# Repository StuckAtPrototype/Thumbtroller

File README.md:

# Thumbtroller - StuckAtPrototype

Remote for the racer car project

https://github.com/StuckAtPrototype/Racer

## Youtube Video
A bit of a back-story of how this project came to be.

Sub if you like what you see.

## Project Structure
The project consists of
1. Firmware
2. Hardware
3. Mechanical 

#### Requirements
- ESP-IDF 5.5
- Git (for cloning ESP-IDF and this repo; see [BUILD_WINDOWS.md](BUILD_WINDOWS.md) if you need to install it)
- Target set to ESP32-H2

**Windows:** See [BUILD_WINDOWS.md](BUILD_WINDOWS.md) for a step-by-step guide: install Git if needed, clone ESP-IDF 5.5, build, and flash the firmware using Command Prompt.

---
## License
### Apache 2.0 -- i.e. use as you'd like
http://www.apache.org/licenses/LICENSE-2.0

--- 
## Special Thanks
Thanks to Michael Angerer for his open sourced `esp32_ble_ota` project. I used it to get BLE running in this project. His blog post and github repo are a great resource. Check it out. https://github.com/michael-angerer/esp32_ble_ota

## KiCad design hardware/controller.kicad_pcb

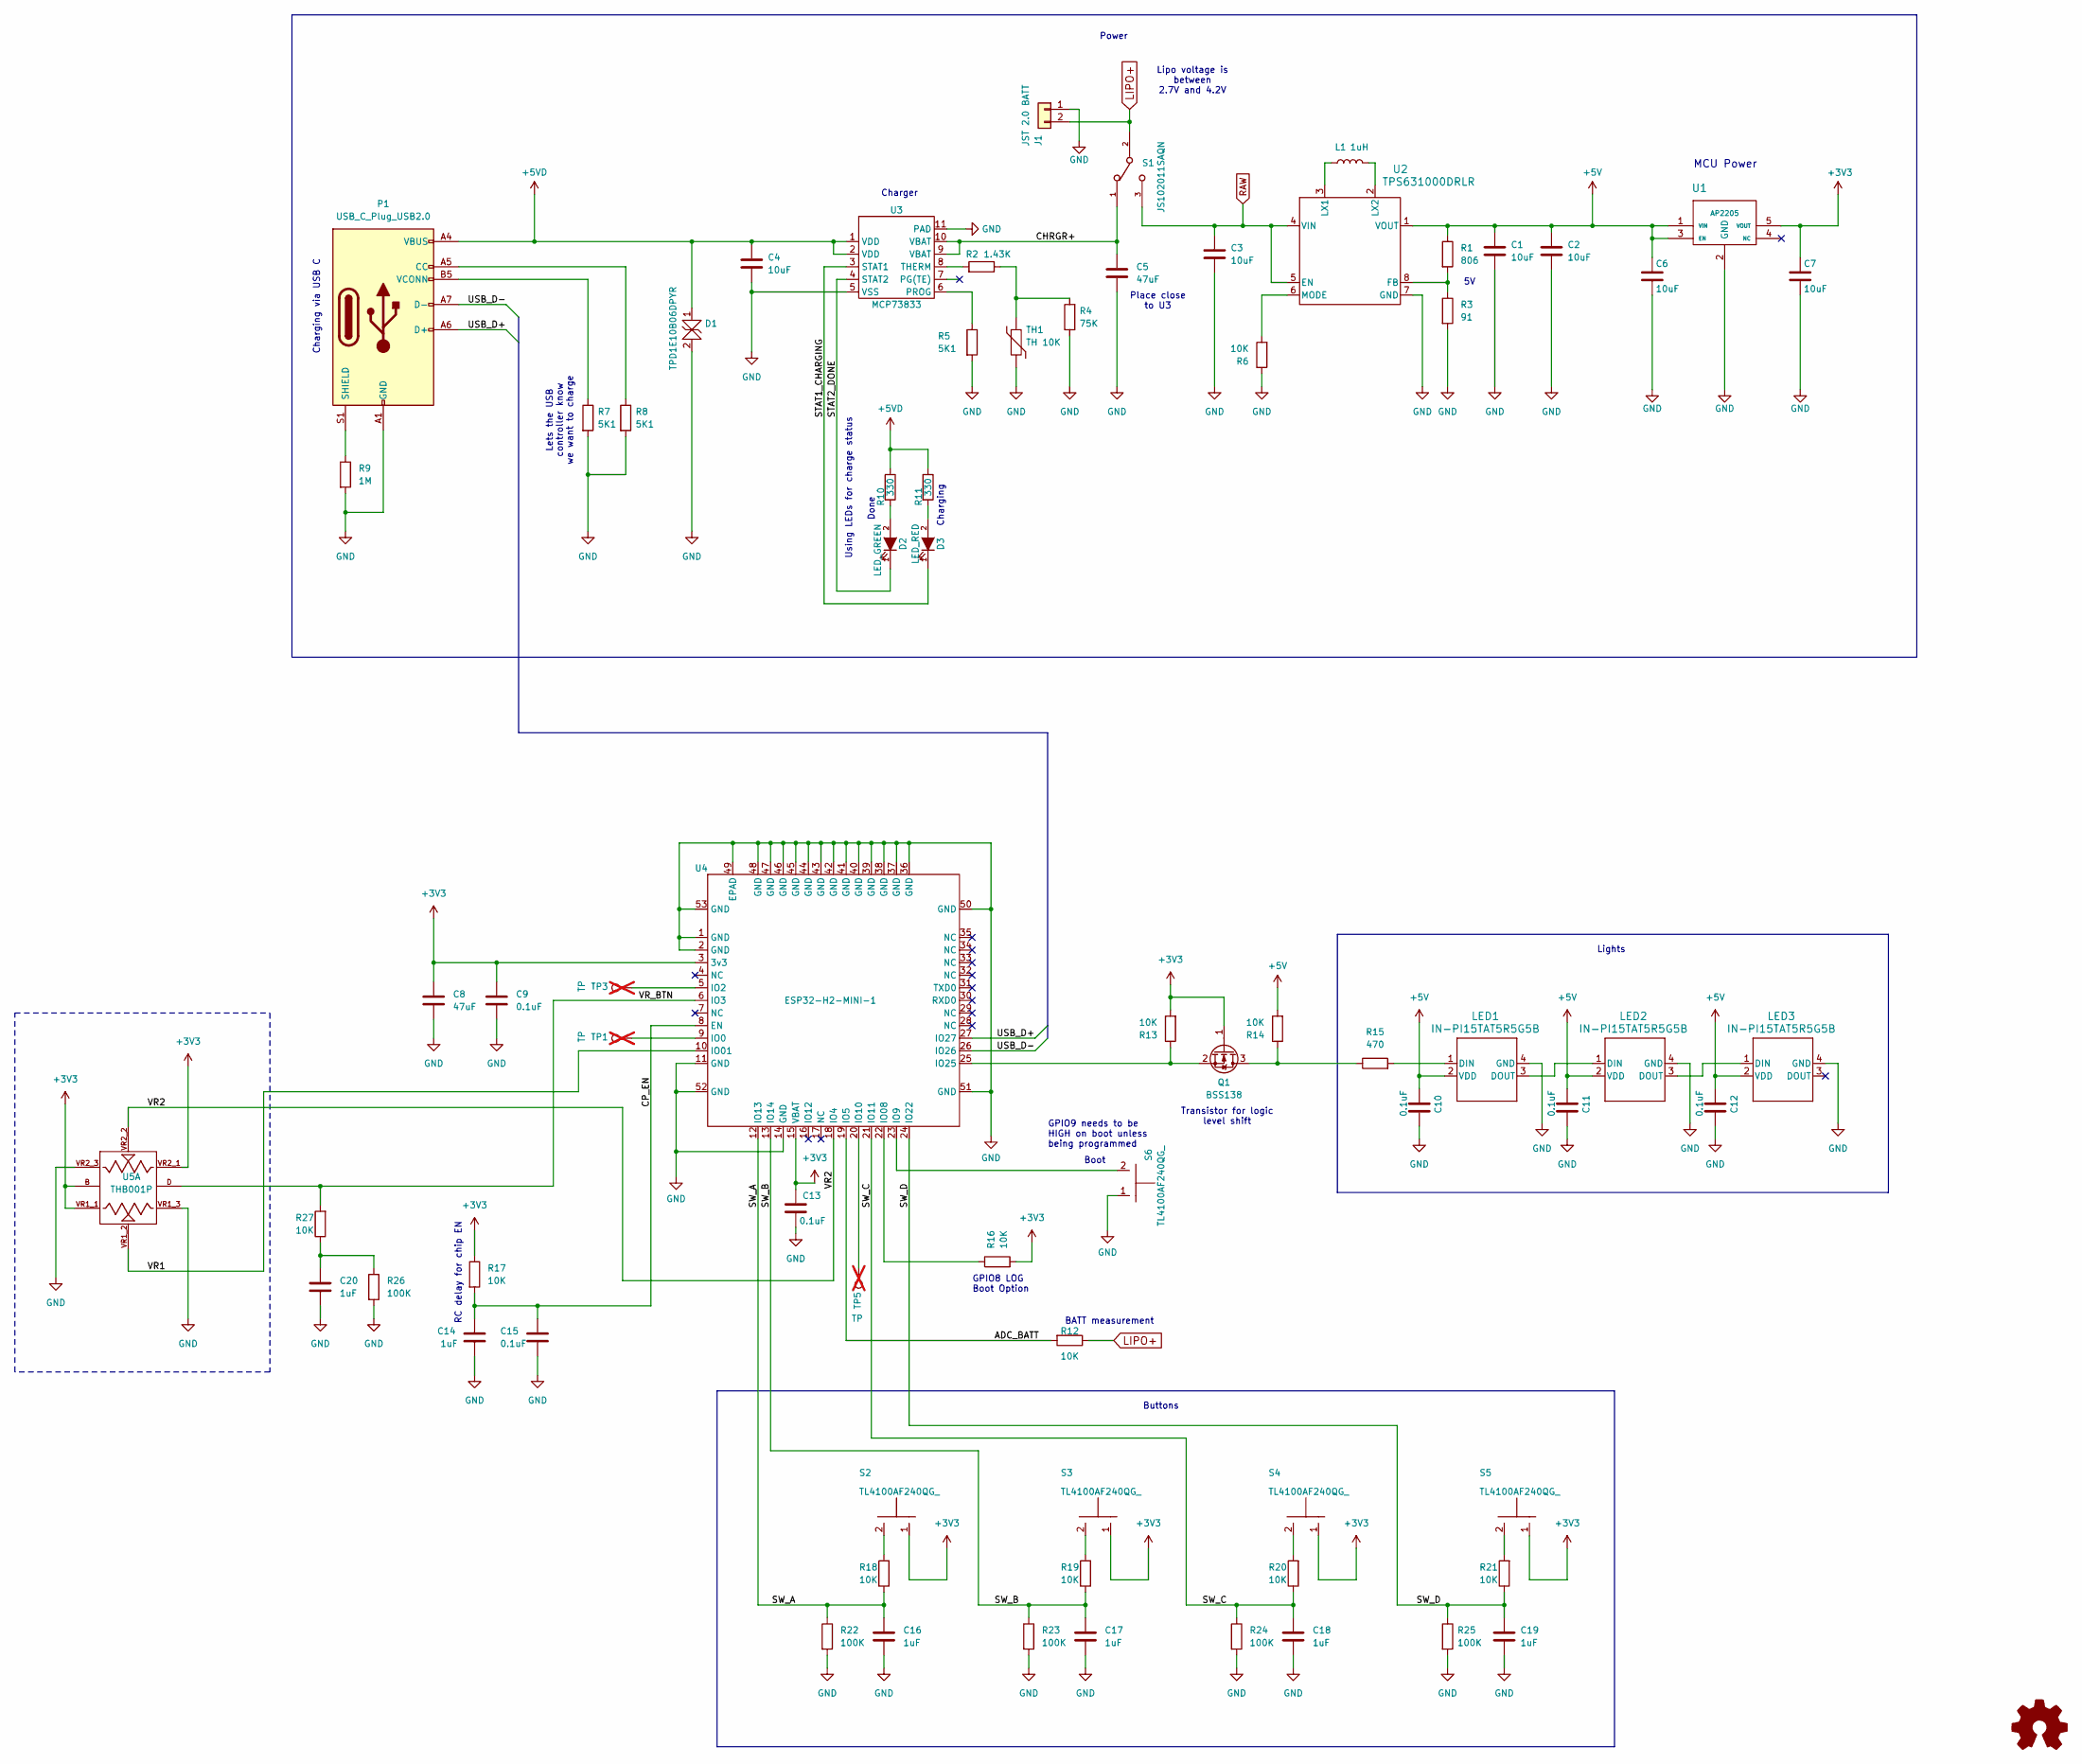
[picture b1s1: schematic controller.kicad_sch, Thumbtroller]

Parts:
C1, C2, C3, C4, C6, C7: 10uF; C_0603_1608Metric
C5, C8: 47uF; C_0603_1608Metric
C9, C10, C11, C12, C13, C15: 0.1uF; C_0603_1608Metric
C14, C16, C17, C18, C19, C20: 1uF; C_0603_1608Metric
D1: TPD1E10B06DPYR; D_SOD-523
D2: LED_GREEN; C_0603_1608Metric
D3: LED_RED; C_0603_1608Metric
J1: JST 2.0 BATT; JST_PH_S2B-PH-SM4-TB_1x02-1MP_P2.00mm_Horizontal
L1: 1uH; RES_CIGT252010
LED1, LED2, LED3: IN-PI15TAT5R5G5B; IN-PI15_INL
P1: USB_C_Plug_USB2.0; GCT_USB4105-GF-A
Q1: BSS138; SOT-23
R1: 806; R_0603_1608Metric
R2: 1.43K; R_0603_1608Metric
R3: 91; R_0603_1608Metric
R4: 75K; R_0603_1608Metric
R5, R7, R8: 5K1; R_0603_1608Metric
R6, R12, R13, R14, R16, R17, R18, R19, R20, R21, R27: 10K; R_0603_1608Metric
R9: 1M; R_0603_1608Metric
R10, R11: 330; R_0603_1608Metric
R15: 470; R_0603_1608Metric
R22, R23, R24, R25, R26: 100K; R_0603_1608Metric
S1: JS102011SAQN; SW_JS102011SAQN
S2, S3, S4, S5, S6: TL4100AF240QG_; SW_PTS810_SJM_250_SMTR_LFS
TH1: TH 10K; R_0603_1608Metric
TP1, TP3, TP5: TP; TestPoint_Pad_1.5x1.5mm; not fitted
U1: AP2205; AP2204
U2: TPS631000DRLR; TPS631000DRLR_TEX
U3: MCP73833; SON50P300X300X100-11N
U4: ESP32-H2-MINI-1; MODULE_ESP32-H2-MINI-1-H2
U5: THB001P; CNK_THB001P; PARTREV 27 Jan 22

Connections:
+3V3: C7.1, C8.1, C9.1, C13.1, Q1.1 (G), R13.2, R16.2, R17.1, S2.1, S3.1, S4.1, S5.1, U1.5 (VOUT), U4.3 (3v3), U4.15 (VBAT), U5.B, U5.VR1_1, U5.VR2_1
+5V: C1.1, C2.1, C6.1, C10.1, C11.1, C12.1, LED1.2 (VDD), LED2.2 (VDD), LED3.2 (VDD), R1.1, R14.2, U1.1 (VIN), U1.3 (EN), U2.1 (VOUT)
+5VD: C4.1, D1.1, P1.A4 (VBUS), P1.A9 (VBUS), P1.B4 (VBUS), P1.B9 (VBUS), R10.1, R11.1, U3.1 (VDD), U3.2 (VDD)
/ADC_BATT: R12.2, U4.19 (IO5)
/CHRGR+: C5.1, S1.1, U3.9 (VBAT), U3.10 (VBAT)
/CP_EN: C14.1, C15.1, R17.2, U4.8 (EN)
/STAT1_CHARGING: D3.1 (K), U3.3 (STAT1)
/STAT2_DONE: D2.1 (K), U3.4 (STAT2)
/SW_A: C16.1, R18.1, R22.1, U4.12 (IO13)
/SW_B: C17.1, R19.1, R23.1, U4.13 (IO14)
/SW_C: C18.1, R20.1, R24.1, U4.21 (IO11)
/SW_D: C19.1, R21.1, R25.1, U4.24 (IO22)
/USB_D+: P1.A6 (D+), U4.27 (IO27)
/USB_D-: P1.A7 (D-), U4.26 (IO26)
/VR1: U4.10 (IO01), U5.VR1_2
/VR2: U4.18 (IO4), U5.VR2_2
/VR_BTN: R27.2, U4.6 (IO3), U5.D
GND: C1.2, C2.2, C3.2, C4.2, C5.2, C6.2, C7.2, C8.2, C9.2, C10.2, C11.2, C12.2, C13.2, C14.2, C15.2, C16.2, C17.2, C18.2, C19.2, C20.2, D1.2, J1.1, LED1.4 (GND), LED2.4 (GND), LED3.4 (GND), P1.A1 (GND), P1.A12 (GND), P1.B1 (GND), P1.B12 (GND), R3.2, R4.1, R5.2, R6.1, R7.2, R8.2, R9.2, R22.2, R23.2, R24.2, R25.2, R26.2, S6.1, TH1.2, U1.2 (GND), U2.7 (GND), U3.5 (VSS), U3.11 (PAD), U4.1 (GND), U4.2 (GND), U4.11 (GND), U4.14 (GND), U4.36 (GND), U4.37 (GND), U4.38 (GND), U4.39 (GND), U4.40 (GND), U4.41 (GND), U4.42 (GND), U4.43 (GND), U4.44 (GND), U4.45 (GND), U4.46 (GND), U4.47 (GND), U4.48 (GND), U4.49 (EPAD), U4.50 (GND), U4.51 (GND), U4.52 (GND), U4.53 (GND), U5.VR1_3, U5.VR2_3
LIPO+: J1.2, R12.1, S1.2
unnamed: C20.1, R26.1, R27.1
unnamed: D2.2 (A), R10.2
unnamed: D3.2 (A), R11.2
unnamed: LED1.1 (DIN), R15.2
unnamed: LED1.3 (DOUT), LED2.1 (DIN)
unnamed: LED2.3 (DOUT), LED3.1 (DIN)
unnamed: P1.A5 (CC), R8.1
unnamed: P1.S1 (SHIELD), R9.1
unnamed: P1.B5 (VCONN), R7.1
unnamed: Q1.3 (D), R14.1, R15.1
unnamed: Q1.2 (S), R13.1, U4.25 (IO25)
unnamed: R2.1, R4.2, TH1.1
unnamed: R18.2, S2.2
unnamed: R19.2, S3.2
unnamed: R20.2, S4.2
unnamed: R21.2, S5.2
unnamed: R1.2, R3.1, U2.8 (FB)
unnamed: L1.1, U2.3 (LX1)
unnamed: L1.2, U2.2 (LX2)
unnamed: R6.2, U2.6 (MODE)
unnamed: R5.1, U3.6 (PROG)
unnamed: R2.2, U3.8 (THERM)
unnamed: TP1.1, U4.9 (IO0)
unnamed: TP3.1, U4.5 (IO2)
unnamed: R16.1, U4.22 (IO08)
unnamed: S6.2, U4.23 (IO9)
unnamed: TP5.1, U4.20 (IO10)
RAW: C3.1, S1.3, U2.4 (VIN), U2.5 (EN)

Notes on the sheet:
Lights
Place close to U3
MCU Power
RC delay for chip EN
Transistor for logic level shift
Charging via USB C
BATT measurement
GPIO8 LOG Boot Option
Boot
GPIO9 needs to be HIGH on boot unless being programmed
Power
Lipo voltage is between 2.7V and 4.2V
Using LEDs for charge status
Charger
Done
Charging
Buttons
Lets the USB controller know we want to charge

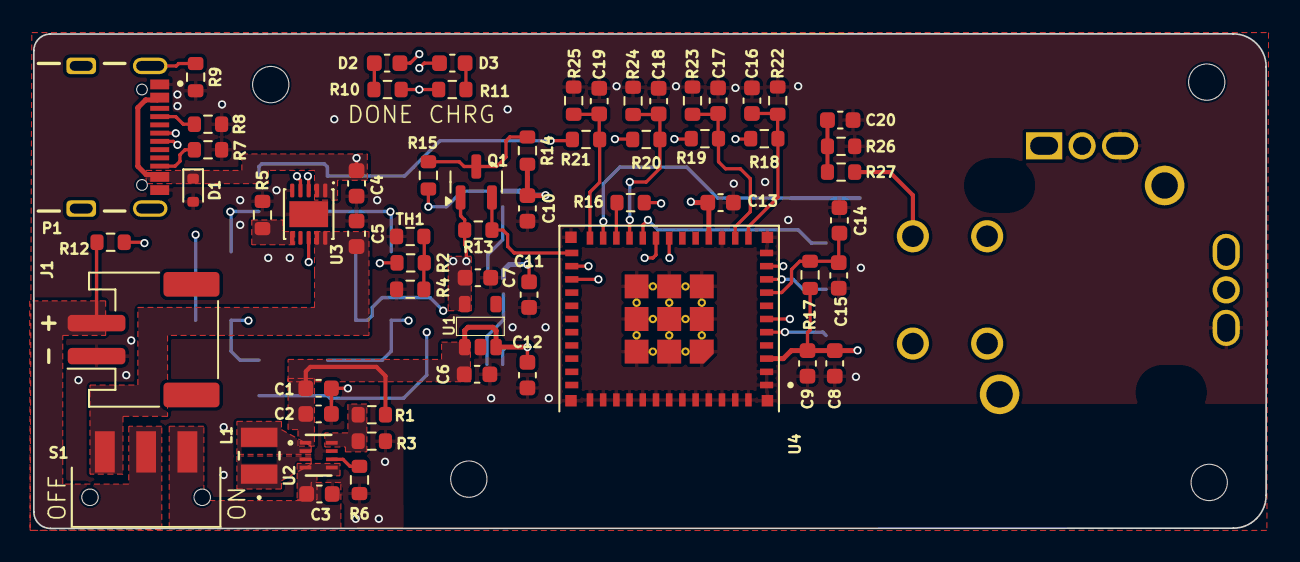
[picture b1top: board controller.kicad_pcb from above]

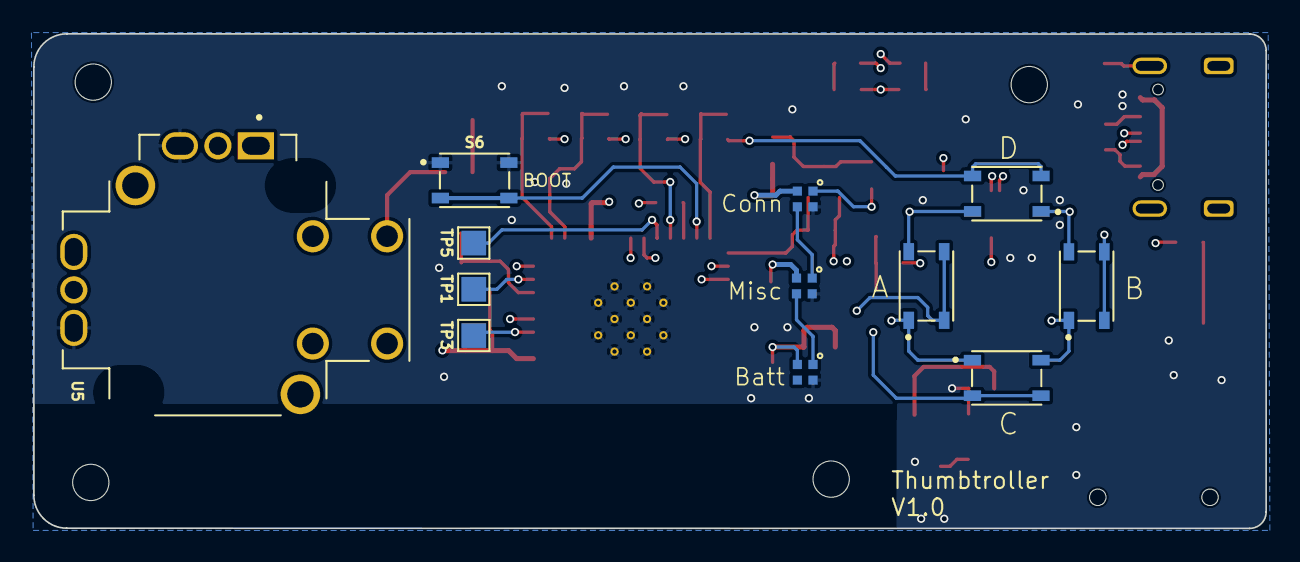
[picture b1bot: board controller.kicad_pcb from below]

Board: 4 copper layers, 74.7 x 30.0 mm, 72 parts (12 on the bottom side), 47 nets.

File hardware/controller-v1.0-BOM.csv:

Designator,Quantity,Manufacturer Part Number,Package/Footprint,Description
C5,1,GRM188R60J226MEA0J,C_0603_1608Metric,22uF
"C16,C20,C18,C17,C19,C14",6,CC0603KRX5R8BB105,C_0603_1608Metric,1uF
"R25,R22,R23,R26,R24",5,WR06X1003FTL,R_0603_1608Metric,100K
"C1,C3,C2,C4,C7",5,GRM188R61A106ME69D,C_0603_1608Metric,10uF
R1,1,RQ73C1J806RBTDF,R_0603_1608Metric,806
"C12,C9,C13,C15,C11,C10",6,CC0603KRX7R7BB104,C_0603_1608Metric,0.1uF
R9,1,RMCF0603FT1M00,R_0603_1608Metric,1M
"R14,R13,R18,R6,R19,R17,R16,R12,R27,R20,R21",11,WR06X103 JTL,R_0603_1608Metric,10K
C8,1,GRM188C80E476ME05D,C_0603_1608Metric,47uF
Q1,1,BSS138,SOT-23,BSS138
"R5,R8,R7",3,RC0603FR-075K1L,R_0603_1608Metric,5K1
U3,1,MCP73833T-AMI/MF,SON50P300X300X100-11N,MCP73833
D3,1,150060RS75000,C_0603_1608Metric,LED_RED
S1,1,JS102011SAQN,SW_JS102011SAQN,JS102011SAQN
R15,1,ESR03EZPF4700,R_0603_1608Metric,470
D2,1,150060GS75000,C_0603_1608Metric,LED_GREEN
R2,1,RT0603BRE071K43L,R_0603_1608Metric,1.43K
U1,1,AP2205-33W5-7,AP2204,AP2205
"R11,R10",2,RC0603JR-07330RL,R_0603_1608Metric,330
J1,1,S2B-PH-SM4-TB,JST_PH_S2B-PH-SM4-TB_1x02-1MP_P2.00mm_Horizontal,JST 2.0 BATT
TH1,1,NTCG163JF103HT1,R_0603_1608Metric,TH 10K
R3,1,CR0603-FX-91R0ELF ,R_0603_1608Metric,91
L1,1,CIGT252010EH1R0MNE,RES_CIGT252010,1uH
D1,1,TPD1E10B06DYAR,D_SOD-523,TPD1E10B06DPYR
U2,1,TPS631000DRLR,TPS631000DRLR_TEX,TPS631000DRLR
C6,1,CL10A225KO8NNNC,C_0603_1608Metric,2.2uF
R4,1,ERJ-PB3B7502V,R_0603_1608Metric,75K
U4,1,ESP32-H2-MINI-1-N4,MODULE_ESP32-H2-MINI-1-H2,ESP32-H2-MINI-1
P1,1,USB4105-GF-A,GCT_USB4105-GF-A,USB_C_Plug_USB2.0
"LED2,LED3,LED1",3,IN-PI15TAT5R5G5B,IN-PI15_INL,IN-PI15TAT5R5G5B
"S5,S3,S4,S2,S6",5,PTS810 SJM 250 SMTR LFS,SW_PTS810_SJM_250_SMTR_LFS,TL4100AF240QG_
U5,1,THB001P,CNK_THB001P,THB001P

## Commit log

2024-10-15 version 0.2
2024-10-19 adding hardware files and BOM for the remote
2024-11-17 Update README.md
    Added Example images of the controller
2025-10-25 firmware v1.0
2025-10-25 3D files v1.0
2025-10-25 hardware v1.0
2026-02-01 adding sdkconfig.defaults
2026-02-02 adding a build guide for windows
